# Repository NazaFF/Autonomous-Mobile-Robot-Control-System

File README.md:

# Autonomous-Mobile-Robot-Control-System
Embedded mobile robotic platform featuring autonomous navigation, obstacle avoidance, light tracking and infrared remote control.

---

# Project Overview

This project presents the design and development of an embedded mobile robotic platform capable of operating in both manual and autonomous modes.

The robot integrates multiple sensing technologies and embedded control algorithms to perform autonomous navigation, obstacle avoidance and light source tracking while also supporting wireless infrared remote control.

The project was developed following a complete engineering workflow, from circuit prototyping and firmware development to PCB design, assembly and system integration.

---

# Project Objectives

- Design a fully functional embedded robotic platform
- Develop a custom PCB
- Integrate multiple sensing technologies
- Implement autonomous navigation algorithms
- Develop wireless infrared remote control
- Implement obstacle avoidance
- Implement light tracking
- Integrate hardware and embedded software

---

# Main Features

- Autonomous obstacle avoidance
- Light source tracking
- Wireless infrared remote control
- DC motor control
- Embedded decision logic
- Real-time sensor acquisition
- Custom PCB
- Arduino-based embedded firmware
- Modular software architecture

---

# Development Process

The project followed an iterative engineering development process.

## Phase 1 — Initial Prototype

The first version was assembled on a breadboard to validate:

- Motor control
- Infrared communication
- Ultrasonic sensor
- Light sensors
- Embedded firmware

📷 **Breadboard Prototype** 

---

## Phase 2 — PCB Design

After validating the prototype, a custom PCB was designed using Autodesk Eagle.

The PCB integrates all sensors, connectors and control electronics required by the robot.

📷 **PCB Schematic**

📷 **PCB Layout**

---

## Phase 3 — PCB Assembly

The PCB was manufactured and assembled by soldering all electronic components.

The board was then integrated into the mobile robot chassis.

📷 **PCB Assembly Image**

---

## Phase 4 — Final Robot

The completed platform integrates:

- Arduino
- Motor Driver
- Infrared Receiver
- Ultrasonic Sensor
- Light Sensors
- Custom PCB
- DC Motors
- Battery Pack

📷 **Robot Image**

---

# Hardware

| Component | Purpose |
|------------|---------|
| Arduino | Main controller |
| DC Motors | Robot locomotion |
| Motor Shield | Motor control |
| Ultrasonic Sensor | Obstacle detection |
| Infrared Receiver | Wireless remote control |
| Photodiodes | Light tracking |
| Custom PCB | Hardware integration |
| Battery Pack | Power supply |

---

# Software

- Arduino IDE
- C++
- Embedded Programming
- Motor Control
- Sensor Processing
- Decision Logic

---

# System Architecture

```text
                  Infrared Remote
                         │
                         ▼
                 Infrared Receiver
                         │
                         ▼
                 Arduino Controller
                         │
       ┌─────────────────┼─────────────────┐
       │                 │                 │
       ▼                 ▼                 ▼
Ultrasonic Sensor   Light Sensors    Motor Driver
       │                                   │
       └─────────────────┬─────────────────┘
                         ▼
                     DC Motors
                         │
                         ▼
                  Mobile Robot Motion
```

---

# Robot Operating Modes

## Manual Mode

The robot is controlled using an infrared remote controller.

The user can:

- Move forward
- Move backward
- Turn left
- Turn right
- Stop

---

## Autonomous Mode

The robot continuously measures the surrounding environment using the ultrasonic sensor.

When an obstacle is detected, the embedded control algorithm selects a new direction to avoid collisions.

---

## Light Tracking Mode

The robot uses two photodiodes to detect the direction of a light source.

The embedded firmware compares both sensor readings and adjusts the robot trajectory accordingly.

---

# Software Architecture

The firmware is organised into multiple functional modules:

- Motor Control
- Obstacle Detection
- Light Tracking
- Infrared Communication
- Robot Motion
- Decision Logic

---

# PCB Design

A dedicated PCB was designed using Autodesk Eagle to improve:

- Reliability
- Mechanical robustness
- Wiring organization
- Ease of assembly

📷 **Eagle Schematic**

📷 **PCB Routing**

---

# Results

The final platform successfully demonstrates:

- Autonomous navigation
- Wireless robot control
- Obstacle avoidance
- Light source tracking
- Embedded software integration
- PCB design and assembly
- Hardware/software integration

---

# Engineering Skills Demonstrated

- Embedded Systems
- Mobile Robotics
- Arduino Programming
- PCB Design
- Schematic Design
- Sensor Integration
- Infrared Communication
- Motor Control
- Embedded Debugging
- Electronics Assembly
- Hardware Integration
- Autonomous Navigation

---

# Challenges

Several engineering challenges were encountered during development:

- Sensor calibration
- Noise filtering
- Infrared communication reliability
- Motor synchronization
- PCB debugging
- Embedded software integration

These challenges were progressively solved through testing, debugging and iterative hardware improvements.

---

# Future Improvements

Possible future developments include:

- Bluetooth control
- Wi-Fi communication
- PID motor control
- Wheel encoders
- Closed-loop navigation
- SLAM algorithms
- Camera vision
- Object detection
- ROS integration

---

# License

This project is licensed under the MIT License.

---

# Author's

**Tomás Ferreira**
**Adriana Pires**

Electrical & Telecommunications Engineers

**Areas of Interest**

- Industrial Automation
- Embedded Systems
- Robotics
- Industrial Electronics
- Control Engineering
- Industry 4.0

Feel free to explore my other engineering projects and connect with me on LinkedIn.

## Contact
- Email: ferreiratomas994@gmail.com
- Outlkook tomasff52@ua.pt
- LinkedIn: (https://www.linkedin.com/in/tomas-ferreira-52635a2b8/?isSelfProfile=true)

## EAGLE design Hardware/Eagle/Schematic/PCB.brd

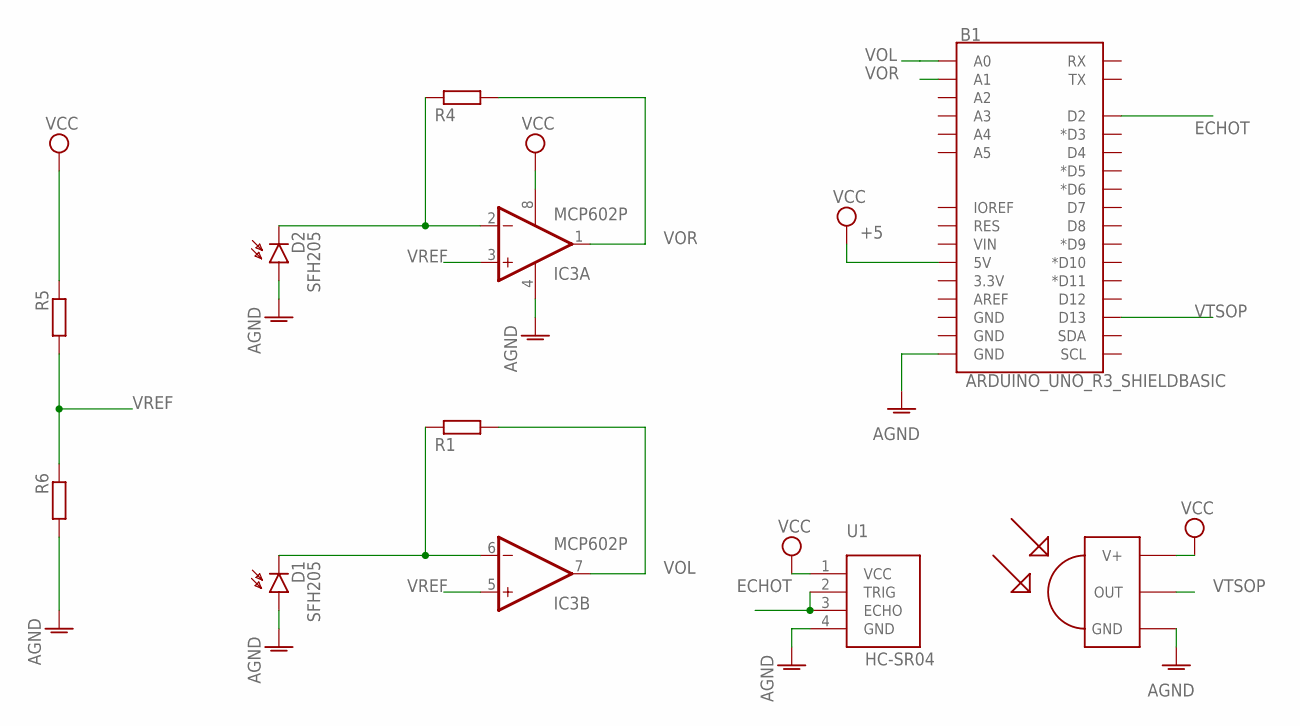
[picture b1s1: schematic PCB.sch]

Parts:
B1: ARDUINO_UNO_R3_SHIELDBASIC; UNO_R3_SHIELD
D1, D2: SFH205
IC3: MCP602P; DIL08
R1, R4, R5, R6: R-EU_0207/10; 0207/10
U1: HC-SR04; XCVR_HC-SR04
U$3: TSOP4856; TSOP18XX

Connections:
AGND: B1.GND@0 (GND), D1.A, D2.A, IC3.4 (V-), R6.2, U1.4 (GND), U$3.GND
ECHOT: B1.D2, U1.2 (TRIG), U1.3 (ECHO)
unnamed: D2.K (C), IC3.2 (-IN), R4.1
unnamed: D1.K (C), IC3.6 (-IN), R1.1
VCC: B1.5V, IC3.8 (V+), R5.1, U1.1 (VCC), U$3.VCC (V+)
VOL: B1.A0, IC3.7 (OUT), R1.2
VOR: B1.A1, IC3.1 (OUT), R4.2
VREF: IC3.3 (+IN), IC3.5 (+IN), R5.2, R6.1
VTSOP: B1.D13, U$3.OUT

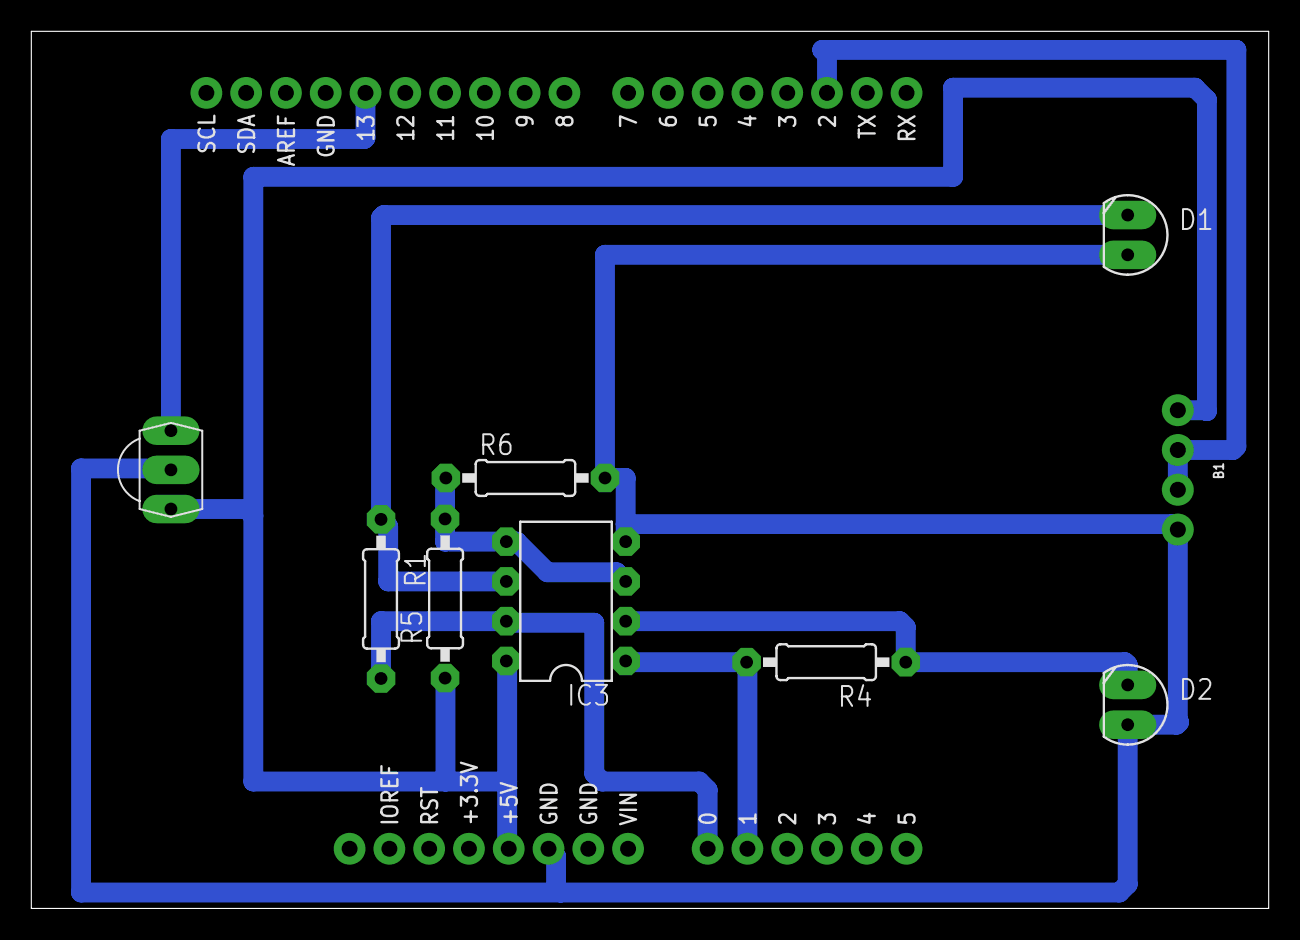
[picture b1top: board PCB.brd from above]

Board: 2 copper layers, 79.0 x 56.0 mm, 10 parts (1 on the bottom side), 9 nets.

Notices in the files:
README.md:
License: MIT
parts and their libraries:
SparkFun-Boards: Licensing: Creative Commons ShareAlike 4.0 International - https://creativecommons.org/licenses/by-sa/4.0
